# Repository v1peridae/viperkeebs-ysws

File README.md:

# viperkeebs-ysws
viperkeebs ysws variant

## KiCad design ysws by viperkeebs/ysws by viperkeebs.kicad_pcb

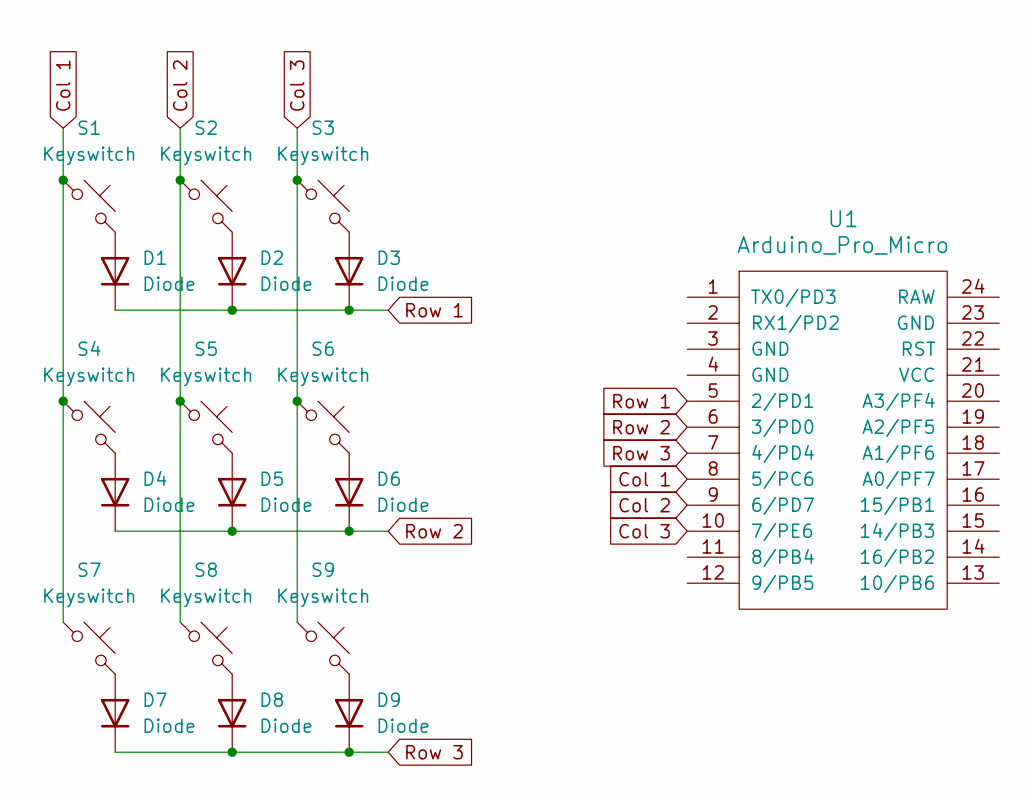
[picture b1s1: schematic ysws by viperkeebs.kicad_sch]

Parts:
D1, D2, D3, D4, D5, D6, D7, D8, D9: Diode; Diode_DO-35
S1, S2, S3, S4, S5, S6, S7, S8, S9: Keyswitch; MX_PCB_1.00u
U1: Arduino_Pro_Micro

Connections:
Col 1: S1.1, S4.1, S7.1, U1.8 (5/PC6)
Col 2: S2.1, S5.1, S8.1, U1.9 (6/PD7)
Col 3: S3.1, S6.1, S9.1, U1.10 (7/PE6)
unnamed: D1.2 (A), S1.2
unnamed: D2.2 (A), S2.2
unnamed: D3.2 (A), S3.2
unnamed: D4.2 (A), S4.2
unnamed: D5.2 (A), S5.2
unnamed: D6.2 (A), S6.2
unnamed: D7.2 (A), S7.2
unnamed: D8.2 (A), S8.2
unnamed: D9.2 (A), S9.2
Row 1: D1.1 (K), D2.1 (K), D3.1 (K), U1.5 (2/PD1)
Row 2: D4.1 (K), D5.1 (K), D6.1 (K), U1.6 (3/PD0)
Row 3: D7.1 (K), D8.1 (K), D9.1 (K), U1.7 (4/PD4)

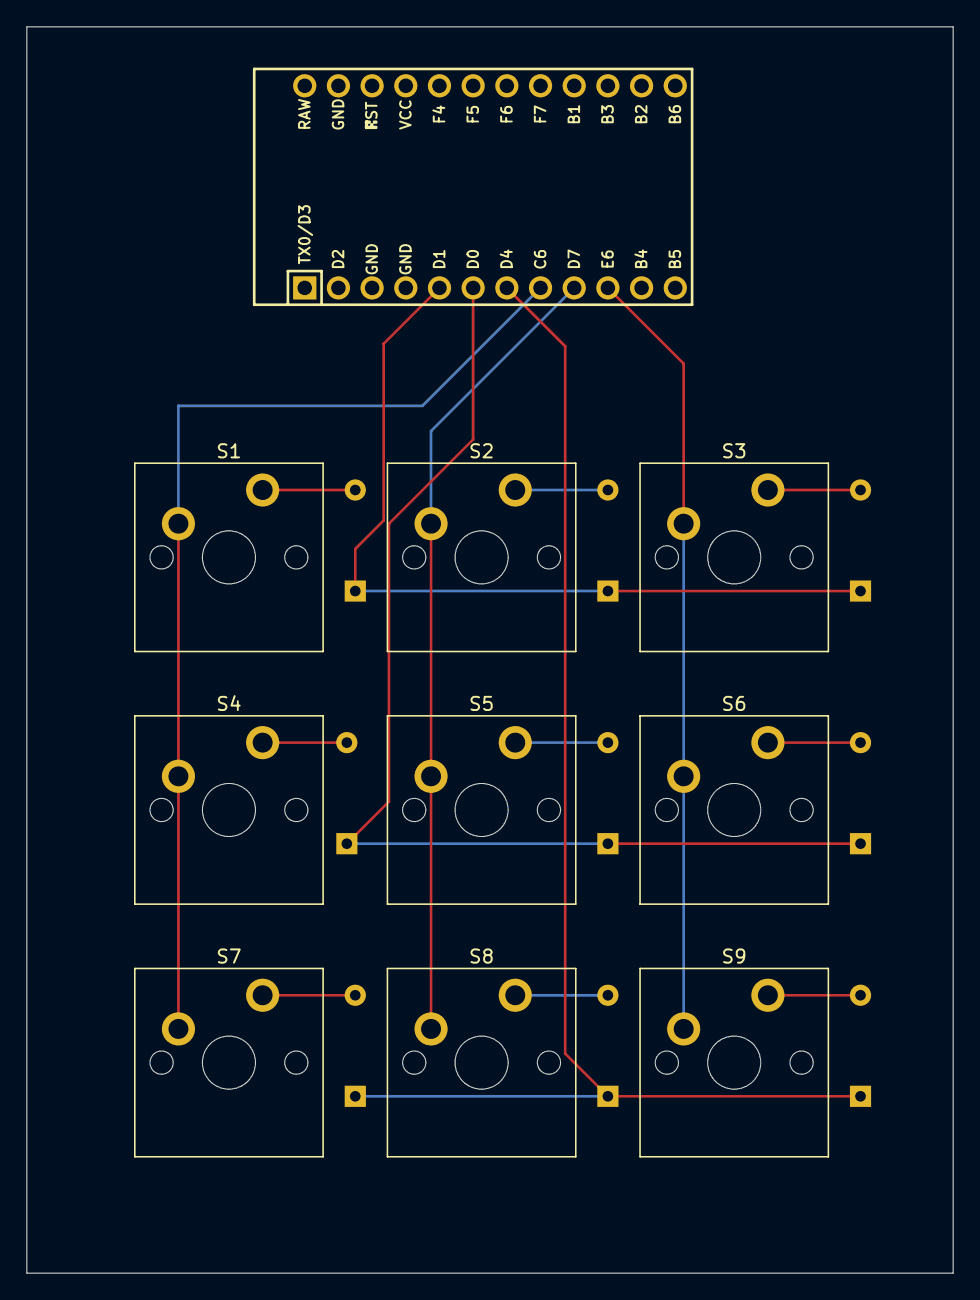
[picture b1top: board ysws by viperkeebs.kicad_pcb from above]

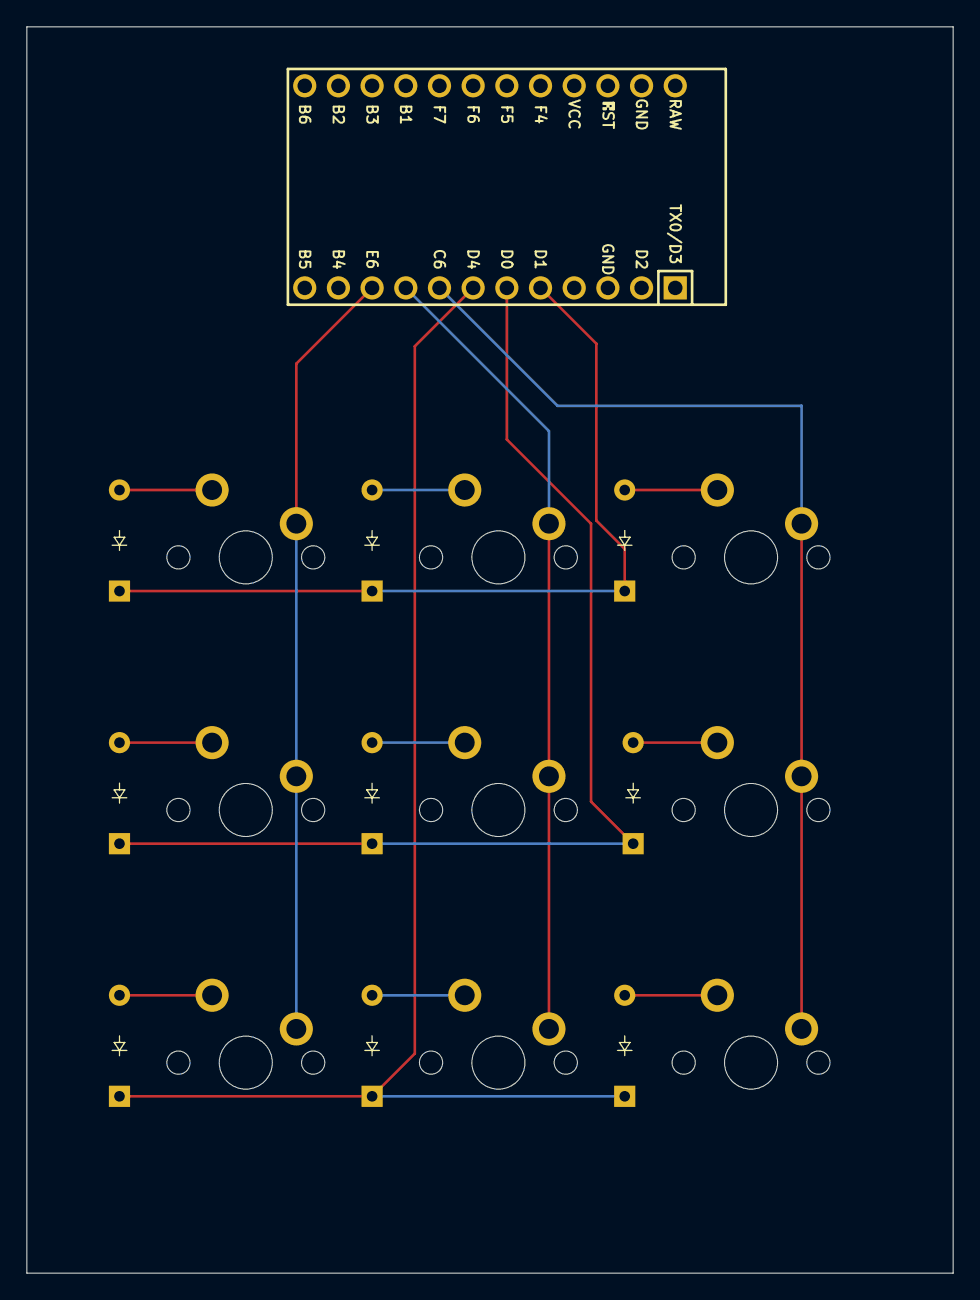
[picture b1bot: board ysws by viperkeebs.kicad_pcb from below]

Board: 2 copper layers, 69.8 x 94.0 mm, 19 parts (9 on the bottom side), 15 nets.
